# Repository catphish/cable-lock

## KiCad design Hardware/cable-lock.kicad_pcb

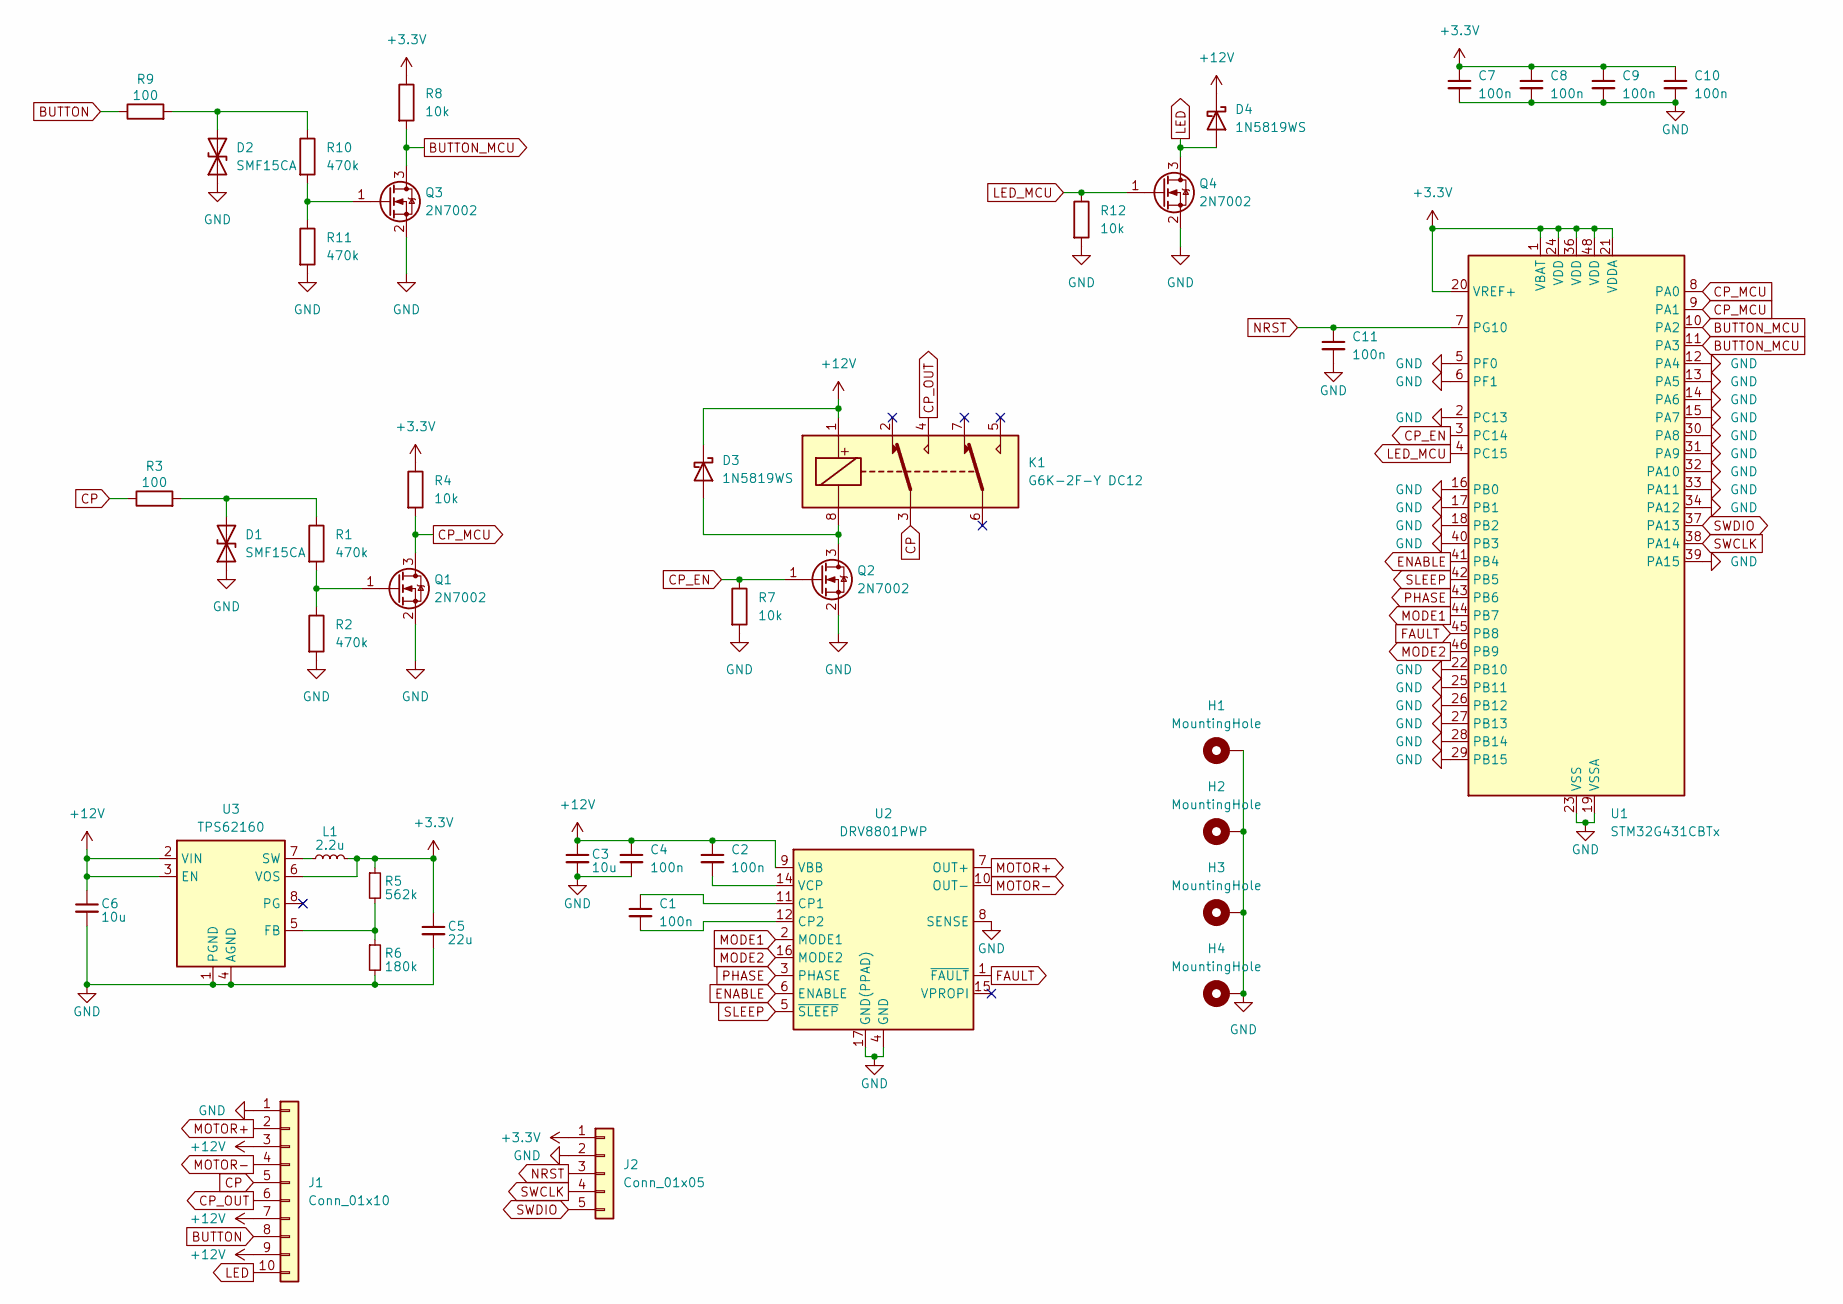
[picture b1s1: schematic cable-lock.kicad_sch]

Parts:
C1, C2, C4, C7, C8, C9, C10, C11: 100n; C_0402_1005Metric; LCSC C1525
C3, C6: 10u; C_1206_3216Metric; LCSC C13585
C5: 22u; C_1206_3216Metric; LCSC C5672
D1, D2: SMF15CA; D_SOD-123F; LCSC C19077510
D3, D4: 1N5819WS; D_SOD-323; LCSC C191023
H1, H2, H3, H4: MountingHole; MountingHole_2.2mm_M2_Pad
J1: Conn_01x10; TerminalBlock_TE_1-282834-0_1x10_P2.54mm_Horizontal; LCSC C918128
J2: Conn_01x05; PinHeader_1x05_P2.54mm_Vertical; LCSC C492404
K1: G6K-2F-Y DC12; Relay_DPDT_Omron_G6K-2F-Y; LCSC C397194
L1: 2.2u; L_Sunlord_SWPA3015S; LCSC C43389
Q1, Q2, Q3, Q4: 2N7002; SOT-23; LCSC C8545
R1, R2, R10, R11: 470k; R_0402_1005Metric; LCSC C25790
R3, R9: 100; R_0402_1005Metric; LCSC C25076
R4, R7, R8, R12: 10k; R_0402_1005Metric; LCSC C25744
R5: 562k; R_0402_1005Metric; LCSC C173826
R6: 180k; R_0402_1005Metric; LCSC C138046
U1: STM32G431CBTx; LQFP-48_7x7mm_P0.5mm; LCSC C529355
U2: DRV8801PWP; HTSSOP-16-1EP_4.4x5mm_P0.65mm_EP3.4x5mm_Mask3x3mm_ThermalVi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; LCSC C41146
U3: TPS62160; MSOP-8_3x3mm_P0.65mm; LCSC C60726

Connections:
+3.3V: C5.1, C7.1, C8.1, C9.1, C10.1, J2.1, L1.2, R4.1, R5.1, R8.1, U1.1 (VBAT), U1.20 (VREF+), U1.21 (VDDA), U1.24 (VDD), U1.36 (VDD), U1.48 (VDD), U3.6 (VOS)
+12V: C2.1, C3.1, C4.1, C6.1, D3.1 (K), D4.1 (K), J1.3, J1.7, J1.9, K1.1, U2.9 (VBB), U3.2 (VIN), U3.3 (EN)
BUTTON: J1.8, R9.1
BUTTON_MCU: Q3.3 (D), R8.2, U1.10 (PA2), U1.11 (PA3)
CP: J1.5, K1.3, R3.1
CP_EN: Q2.1 (G), R7.1, U1.3 (PC14)
CP_MCU: Q1.3 (D), R4.2, U1.8 (PA0), U1.9 (PA1)
CP_OUT: J1.6, K1.4
ENABLE: U1.41 (PB4), U2.6 (ENABLE)
FAULT: U1.45 (PB8), U2.1 (~FAULT)
GND: C3.2, C4.2, C5.2, C6.2, C7.2, C8.2, C9.2, C10.2, C11.2, D1.1 (A1), D2.1 (A1), H1.1, H2.1, H3.1, H4.1, J1.1, J2.2, Q1.2 (S), Q2.2 (S), Q3.2 (S), Q4.2 (S), R2.2, R6.2, R7.2, R11.2, R12.2, U1.2 (PC13), U1.5 (PF0), U1.6 (PF1), U1.12 (PA4), U1.13 (PA5), U1.14 (PA6), U1.15 (PA7), U1.16 (PB0), U1.17 (PB1), U1.18 (PB2), U1.19 (VSSA), U1.22 (PB10), U1.23 (VSS), U1.25 (PB11), U1.26 (PB12), U1.27 (PB13), U1.28 (PB14), U1.29 (PB15), U1.30 (PA8), U1.31 (PA9), U1.32 (PA10), U1.33 (PA11), U1.34 (PA12), U1.35 (VSS), U1.39 (PA15), U1.40 (PB3), U1.47 (VSS), U2.4 (GND), U2.8 (SENSE), U2.13 (GND), U2.17 (GND(PPAD)), U3.1 (PGND), U3.4 (AGND)
LED: D4.2 (A), J1.10, Q4.3 (D)
LED_MCU: Q4.1 (G), R12.1, U1.4 (PC15)
MODE1: U1.44 (PB7), U2.2 (MODE1)
MODE2: U1.46 (PB9), U2.16 (MODE2)
MOTOR+: J1.2, U2.7 (OUT+)
MOTOR-: J1.4, U2.10 (OUT-)
NRST: C11.1, J2.3, U1.7 (PG10)
unnamed: D1.2 (A2), R1.1, R3.2
unnamed: D2.2 (A2), R9.2, R10.1
unnamed: D3.2 (A), K1.8, Q2.3 (D)
unnamed: Q1.1 (G), R1.2, R2.1
unnamed: Q3.1 (G), R10.2, R11.1
unnamed: C1.1, U2.11 (CP1)
unnamed: C1.2, U2.12 (CP2)
unnamed: C2.2, U2.14 (VCP)
unnamed: R5.2, R6.1, U3.5 (FB)
unnamed: L1.1, U3.7 (SW)
PHASE: U1.43 (PB6), U2.3 (PHASE)
SLEEP: U1.42 (PB5), U2.5 (~SLEEP)
SWCLK: J2.4, U1.38 (PA14)
SWDIO: J2.5, U1.37 (PA13)

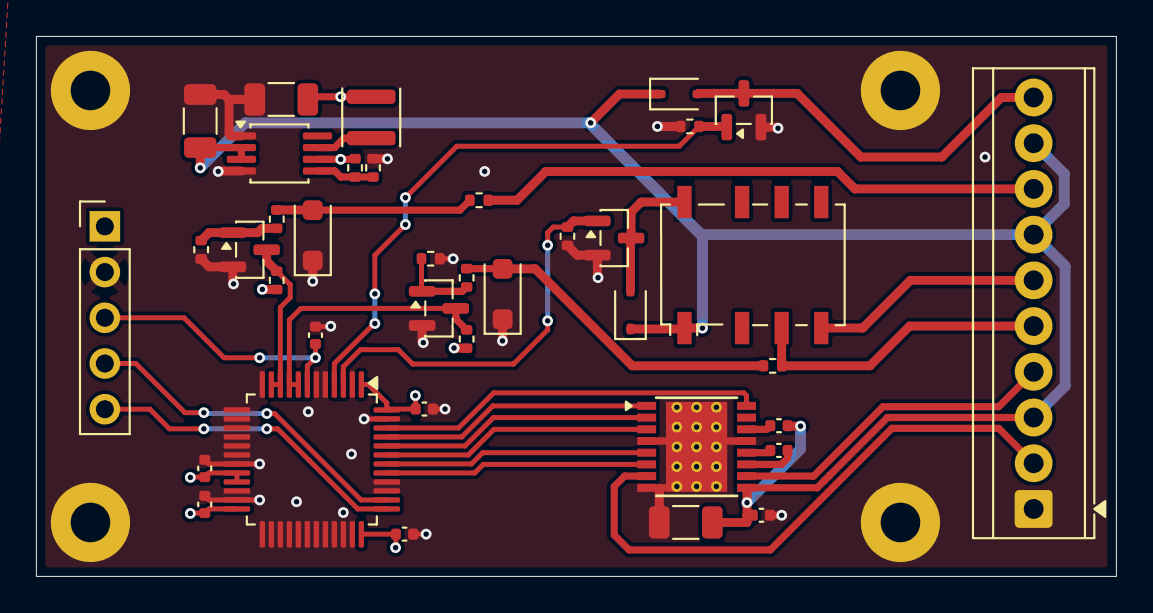
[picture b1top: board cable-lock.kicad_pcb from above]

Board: 4 copper layers, 60.0 x 30.0 mm, 42 parts (0 on the bottom side), 32 nets.

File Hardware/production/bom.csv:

Designator,Footprint,Quantity,Value,LCSC Part #
"C1, C10, C11, C2, C4, C7, C8, C9",0402,8,100n,C1525
"C3, C6",1206,2,10u,C13585
C5,1206,1,22u,C5672
"D1, D2",D_SOD-123F,2,SMF15CA,C19077510
"D3, D4",D_SOD-323,2,1N5819WS,C191023
J1,TerminalBlock_TE_1-282834-0_1x10_P2.54mm_Horizontal,1,Conn_01x10,C918128
J2,PinHeader_1x05_P2.54mm_Vertical,1,Conn_01x05,C492404
K1,Relay_DPDT_Omron_G6K-2F-Y,1,G6K-2F-Y DC12,C397194
L1,L_Sunlord_SWPA3015S,1,2.2u,C43389
"Q1, Q2, Q3, Q4",SOT-23,4,2N7002,C8545
"R1, R10, R11, R2",0402,4,470k,C25790
"R12, R4, R7, R8",0402,4,10k,C25744
"R3, R9",0402,2,100,C25076
R5,0402,1,562k,C173826
R6,0402,1,180k,C138046
U1,LQFP-48_7x7mm_P0.5mm,1,STM32G431CBTx,C529355
U2,HTSSOP-16-1EP_4.4x5mm_P0.65mm_EP3.4x5mm_Mask3x3mm_ThermalVias,1,DRV8801PWP,C41146
U3,MSOP-8_3x3mm_P0.65mm,1,TPS62160,C60726

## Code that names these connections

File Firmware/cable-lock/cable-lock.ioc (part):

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Mcu.Name=STM32G431C(6-8-B)Tx
Mcu.Package=LQFP48
Mcu.UserName=STM32G431CBTx
PA0.GPIOParameters=GPIO_Label
PA0.GPIO_Label=CP_WKUP
PA0.Mode=SYS_WakeUp0
PA0.Signal=SYS_WKUP1
PA1.GPIOParameters=GPIO_Label
PA1.GPIO_Label=CP
PA1.Signal=GPIO_Input
PA13.Mode=Serial_Wire
PA13.Signal=SYS_JTMS-SWDIO
PA14.Mode=Serial_Wire
PA14.Signal=SYS_JTCK-SWCLK
PA2.GPIOParameters=GPIO_Label
PA2.GPIO_Label=BUTTON_WKUP
PA2.Mode=SYS_WakeUp3
PA2.Signal=SYS_WKUP4
PA3.GPIOParameters=GPIO_Label
PA3.GPIO_Label=BUTTON
PA3.Signal=GPIO_Input
PB4.GPIOParameters=GPIO_Label
PB4.GPIO_Label=MOTOR_ENABLE
PB4.Signal=GPIO_Output
PB5.GPIOParameters=GPIO_Label
PB5.GPIO_Label=MOTOR_SLEEP
PB5.Signal=GPIO_Output
PB6.GPIOParameters=GPIO_Label
PB6.GPIO_Label=MOTOR_PHASE
PB6.Signal=GPIO_Output
PB7.GPIOParameters=GPIO_Label
PB7.GPIO_Label=MOTOR_MODE1
PB7.Signal=GPIO_Output
PB8-BOOT0.GPIOParameters=GPIO_Label
PB8-BOOT0.GPIO_Label=MOTOR_FAULT
PB8-BOOT0.Signal=GPIO_Input
PB9.GPIOParameters=GPIO_Label
PB9.GPIO_Label=MOTOR_MODE2
PB9.Signal=GPIO_Output
PC14-OSC32_IN.GPIOParameters=GPIO_Label
PC14-OSC32_IN.GPIO_Label=RELAY
PC14-OSC32_IN.Signal=GPIO_Output
PC15-OSC32_OUT.GPIOParameters=GPIO_Label
PC15-OSC32_OUT.GPIO_Label=LED
PC15-OSC32_OUT.Signal=GPIO_Output
RCC.HSE_VALUE=8000000
RCC.SYSCLKFreq_VALUE=16000000
board=custom

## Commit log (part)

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2026-04-29 initial commit, v1 hardware order
